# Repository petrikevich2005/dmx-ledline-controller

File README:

этот репозиторий создан для хранения файлов проекта https://docs.google.com/document/d/1fRXYH3zwlAKKTRARIA5Y8lPj13gHvqdowoUjWwAMtXU/edit?usp=sharing

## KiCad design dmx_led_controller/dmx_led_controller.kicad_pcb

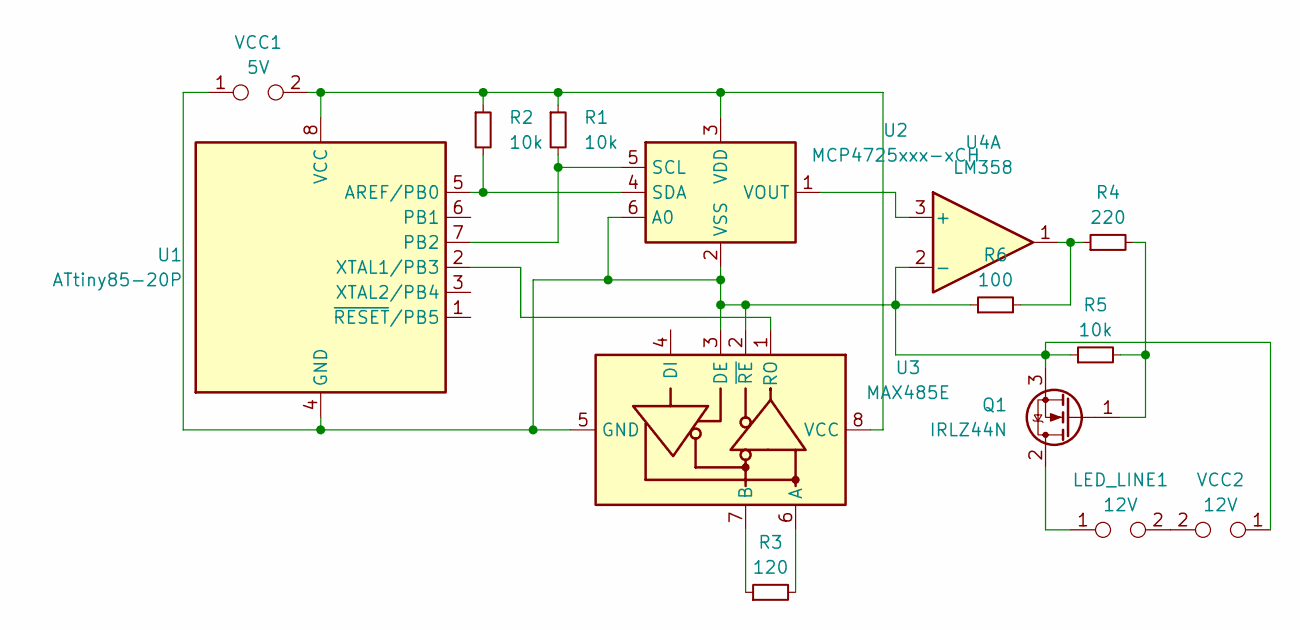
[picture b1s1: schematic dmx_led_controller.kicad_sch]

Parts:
LED_LINE1: 12V; TestPoint 2pin
Q1: IRLZ44N; TO-220-3_Vertical
R1, R2, R5: 10k; R_0805_2012Metric
R3: 120; R_0805_2012Metric
R4: 220; R_0805_2012Metric
R6: 100; R_0805_2012Metric
U1: ATtiny85-20P; DIP-8_W7.62mm
U2: MCP4725xxx-xCH; SOT-23-6
U3: MAX485E; SOIC-8_3.9x4.9mm_P1.27mm
U4: LM358; DIP-8_W7.62mm
VCC1: 5V; TestPoint 2pin
VCC2: 12V; TestPoint 2pin

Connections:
unnamed: LED_LINE1.2, VCC2.2
unnamed: LED_LINE1.1, Q1.2 (D)
unnamed: Q1.1 (G), R4.2, R5.2
unnamed: Q1.3 (S), R5.1, R6.1, U1.4 (GND), U2.2 (VSS), U2.6 (A0), U3.2 (~RE), U3.3 (DE), U3.5 (GND), U4.2 (-), VCC1.1, VCC2.1
unnamed: R4.1, R6.2, U4.1
unnamed: R2.2, U1.5 (AREF/PB0), U2.4 (SDA)
unnamed: R1.2, U1.7 (PB2), U2.5 (SCL)
unnamed: R1.1, R2.1, U1.8 (VCC), U2.3 (VDD), U3.8 (VCC), VCC1.2
unnamed: U1.2 (XTAL1/PB3), U3.1 (RO)
unnamed: U2.1 (VOUT), U4.3 (+)
unnamed: R3.2, U3.6 (A)
unnamed: R3.1, U3.7 (B)

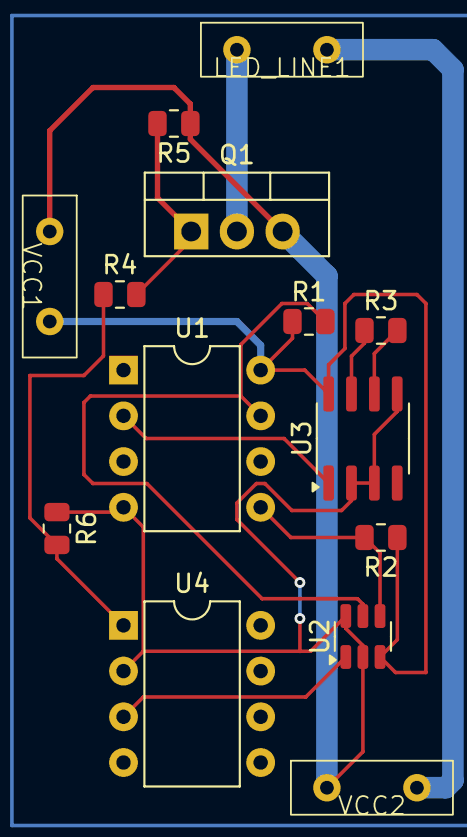
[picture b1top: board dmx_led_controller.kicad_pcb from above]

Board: 2 copper layers, 14 parts (0 on the bottom side), 12 nets.

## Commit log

2025-03-06 make pcb
